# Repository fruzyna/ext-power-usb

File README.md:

# ext-power-usb
PCB for an externally powered USB pass-through

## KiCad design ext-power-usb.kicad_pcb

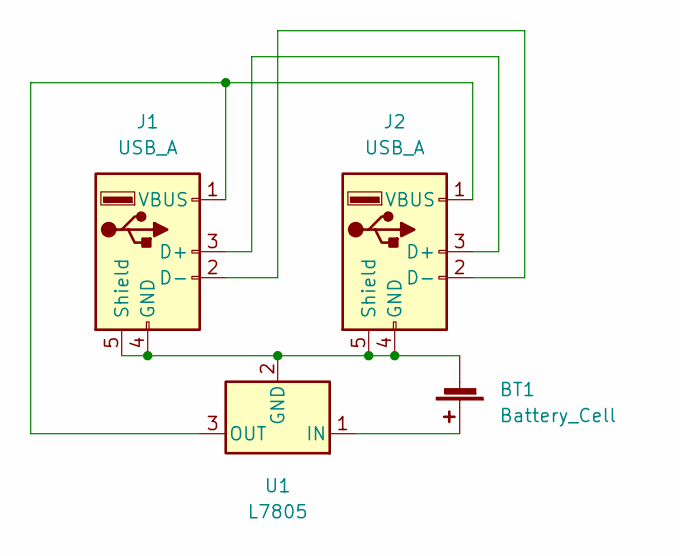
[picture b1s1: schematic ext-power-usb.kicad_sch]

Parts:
BT1: Battery_Cell; PinHeader_1x02_P2.54mm_Vertical
J1, J2: USB_A; USB_A_Molex_67643_Horizontal
U1: L7805; TO-220-3_Horizontal_TabUp

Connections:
unnamed: BT1.1 (+), U1.1 (IN)
unnamed: J1.1 (VBUS), J2.1 (VBUS), U1.3 (OUT)
unnamed: J1.2 (D-), J2.2 (D-)
unnamed: J1.3 (D+), J2.3 (D+)
unnamed: BT1.2 (-), J1.4 (GND), J1.5 (Shield), J2.4 (GND), J2.5 (Shield), U1.2 (GND)

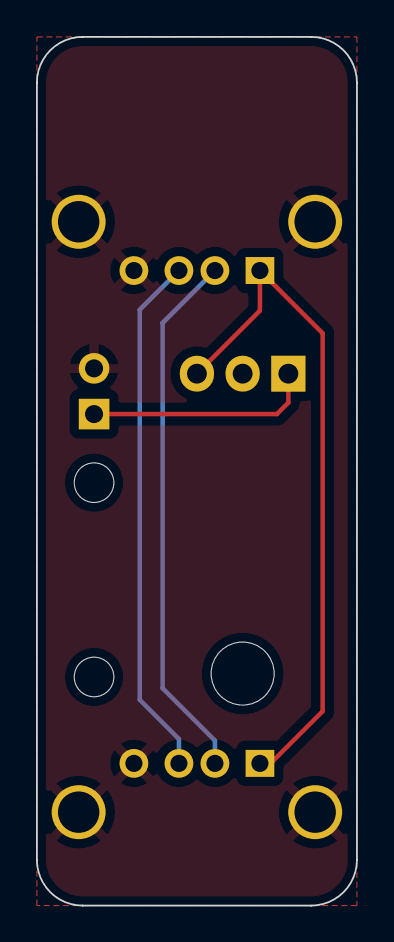
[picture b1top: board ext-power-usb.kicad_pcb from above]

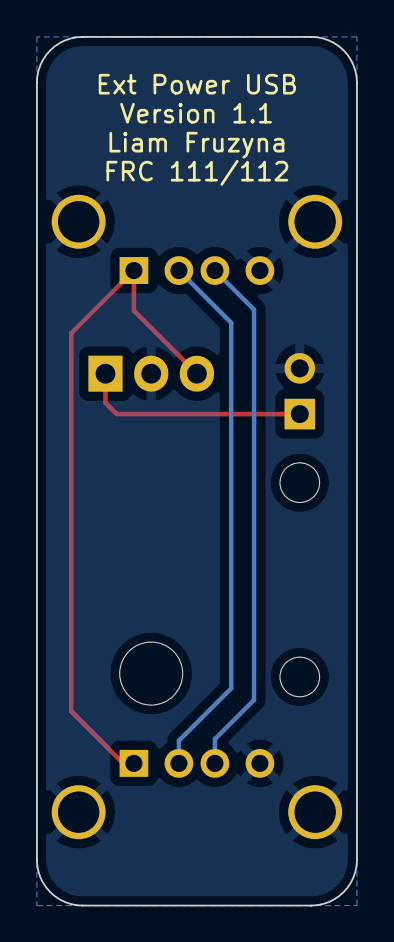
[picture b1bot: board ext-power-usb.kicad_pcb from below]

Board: 2 copper layers, 17.8 x 48.3 mm, 4 parts (2 on the bottom side), 5 nets.

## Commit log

2023-04-16 Added kicad files
2023-04-27 Shifted USB plug deeper onto board, adjusted position of input power
